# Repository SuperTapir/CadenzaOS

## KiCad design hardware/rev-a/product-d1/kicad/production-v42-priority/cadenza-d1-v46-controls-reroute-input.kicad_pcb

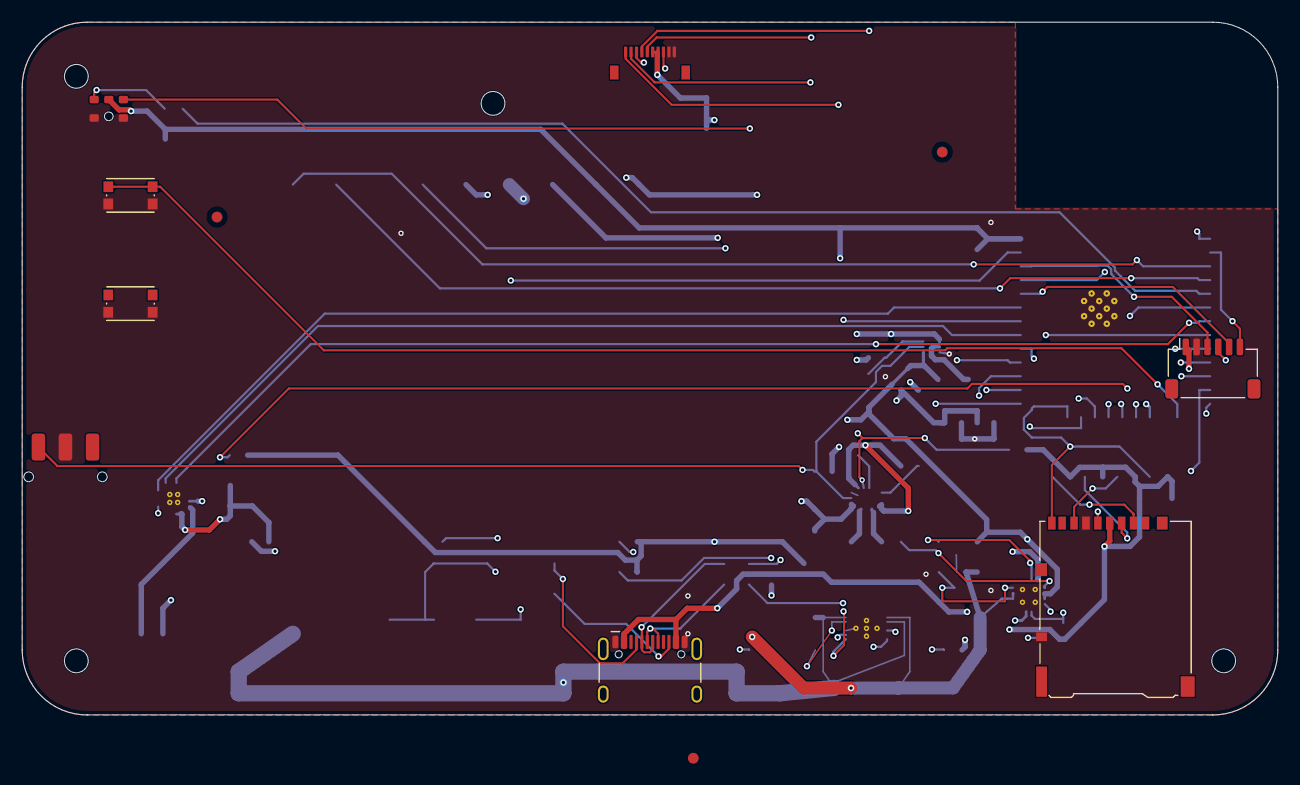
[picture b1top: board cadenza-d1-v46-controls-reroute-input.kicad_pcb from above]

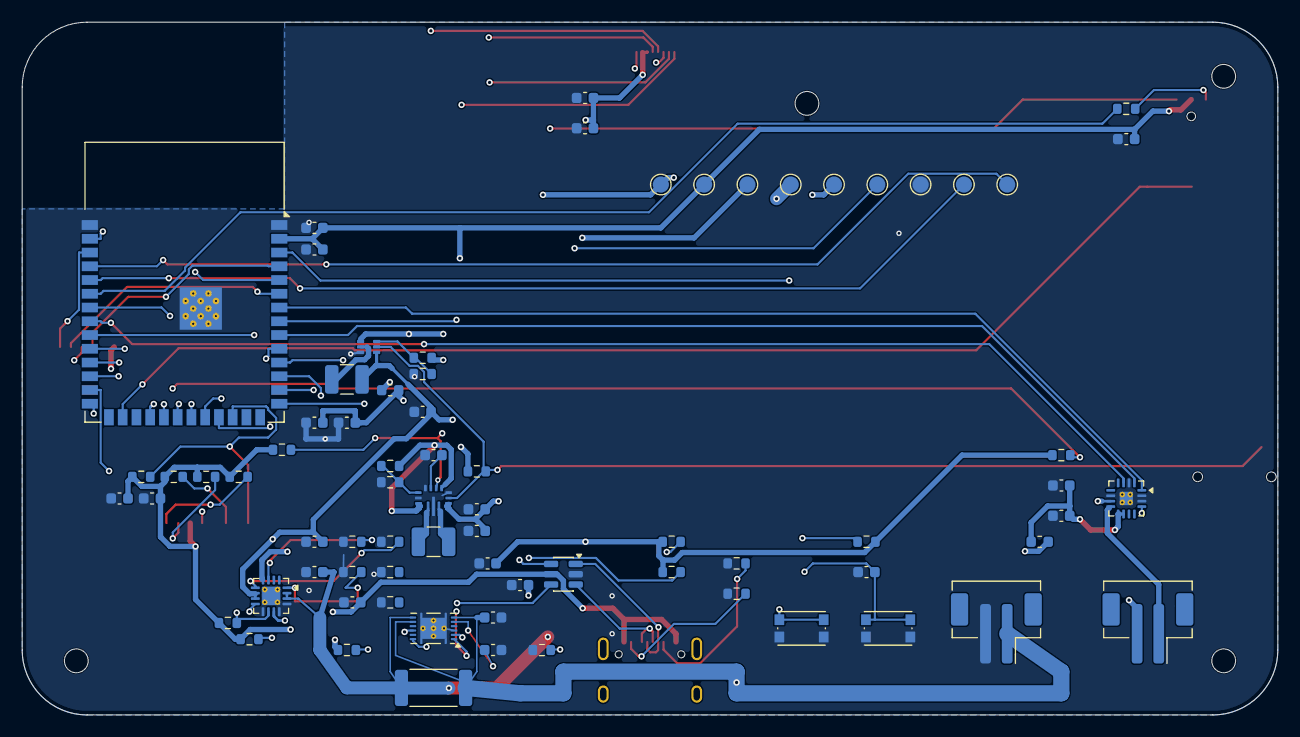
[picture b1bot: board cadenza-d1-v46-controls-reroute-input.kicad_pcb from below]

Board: 4 copper layers, 116.0 x 64.0 mm, 90 parts (74 on the bottom side), 65 nets.

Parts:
C1, C2, C3, C10, C11, C20, C50, C81, C90: 10uF
C12, C13, C21, C22: 22uF
C14, C31, C40, C51, C82, C91: 100nF
C30, C70, C71, C80: 1uF
FB1, FB2: 600R@100MHz
FID1, FID2, FID3: Fiducial; Fiducial_1mm_Mask2mm
H1, H2, H3, H4: NPTH 2.2mm
J1: USB-C USB2 Sink
J2: LS027B7DH01 FPC
J3: microSD push-push
J4: LiPo 1S
J5: Speaker 8R 1-2W
J6: Encoder daughterboard
L1: 1.2uH Isat>=4.5A
L2: 1uH Isat>=4.5A
LCD1: LS027B7DH01 62.8x42.82
R1, R2: 5.1k
R3, R5: 1.5k
R4: 1.18k
R6: 47k
R7, R72, R74, R80, R90, R91, R92, R93: 10k
R10: 470k
R11: 150k
R20: 732k
R21, R30, R41, R75, R76, R77: 100k
R40: 100R
R70, R71: 4.7k
R73: 0.01R 1% 1W 50ppm; R_2512_6332Metric
SW1: POWER RUN/OFF
SW2: B
SW3: MENU
SW4: RESET
SW5: BOOT
TP1: UART_TX0; TestPoint_Pad_D1.5mm
TP2: UART_RX0; TestPoint_Pad_D1.5mm
TP3: GND; TestPoint_Pad_D1.5mm
TP4: PG_3V3; TestPoint_Pad_D1.5mm
TP5: PACKP; TestPoint_Pad_D1.5mm
TP6: VBAT; TestPoint_Pad_D1.5mm
TP7: VSYS; TestPoint_Pad_D1.5mm
TP8: +3V3; TestPoint_Pad_D1.5mm
TP9: +5V; TestPoint_Pad_D1.5mm
U1: ESP32-S3-WROOM-1-N16R8
U2: BQ24074RGTR
U3: TPS63070RNMR
U4: TPS61023DRLR
U5: MAX98357AETE+T
U6: IM73D122V01
U7: BQ27441DRZR-G1A
U8: USBLC6-2SC6

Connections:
/+3V3_MAIN: C12.1, C13.1, C40.1, C81.1, C82.1, C90.1, C91.1, J3.4 (VDD), J6.1, R10.1, R41.2, R70.2, R71.2, R74.2, R75.2, R76.2, R77.2, R80.1, R90.2, R91.2, R92.2, R93.2, TP8.1, U1.2 (3V3), U3.1 (PS_SYNC), U3.7 (VOUT), U3.8 (VOUT), U6.2 (VDD)
/+5V_AUDIO: C50.1, C51.1, FB2.2, U5.7 (VDD), U5.8 (VDD)
/+5V_LCD: C30.1, C31.1, FB1.2, J2.6 (VDDA), J2.7 (VDD)
/+5V_MEDIA: C21.1, C22.1, FB1.1, FB2.1, R20.1, TP9.1, U4.6 (VOUT)
/AMP_EN: R41.1, U1.34 (GPIO41), U5.4 (SD_MODE)
/A_SW: J6.5, U1.6 (GPIO6)
/BAT_TS: R7.1, U2.1 (TS)
/BOOST_SW: L2.2, U4.5 (SW)
/BOOT_N: SW5.1 (A), U1.27 (GPIO0)
/B_SW: SW2.1 (A), U1.24 (GPIO47)
/CC1: J1.A5 (CC1), R1.1
/CC2: J1.B5 (CC2), R2.1
/CHG_N: R77.1, U1.10 (GPIO17), U2.9 (CHG)
/ENC_A: J6.3, U1.4 (GPIO4)
/ENC_B: J6.4, U1.5 (GPIO5)
/ESP_EN: C80.1, R80.2, SW4.1 (A), U1.3 (EN)
/FB_3V3: R10.2, R11.1, U3.5 (FB)
/FB_5V: R20.2, R21.1, U4.1 (FB)
/GAUGE_BIN: R72.1, U7.10 (NC)
/GAUGE_INT_N: R74.1, U1.23 (GPIO21), U7.12 (GPOUT)
/GAUGE_VDD: C71.1, U7.5 (SCL)
/GND: C1.2, C2.2, C3.2, C10.2, C11.2, C12.2, C13.2, C14.2, C20.2, C21.2, C22.2, C30.2, C31.2, C40.2, C50.2, C51.2, C70.2, C71.2, C80.2, C81.2, C82.2, C90.2, C91.2, J1.A1 (GND), J1.A12 (GND), J1.B1 (GND), J1.B12 (GND), J2.9 (VSS), J2.10 (VSSA), J3.6 (VSS), J3.10 (SHIELD), J4.2, J6.2, R1.2, R2.2, R3.2, R4.2, R5.2, R6.2, R7.2, R11.2, R21.2, R72.2, SW1.2 (B), SW2.2 (B), SW3.2 (B), SW4.2 (B), SW5.2 (B), TP3.1, U1.1 (GND), U1.40 (GND), U1.41 (EPAD), U2.4 (CE), U2.5 (EN2), U2.8 (VSS), U2.17 (EP), U3.4 (GND), U3.6 (FB2), U3.10 (PGND), U3.15 (VSEL), U4.4 (GND), U5.2 (GAIN_SLOT), U5.3 (GND), U5.11 (GND), U5.15 (GND), U5.17 (EP), U6.4 (LR), U6.5 (GND), U7.3 (NC), U7.13 (EP), U8.2 (GND)
/I2C_SCL: R71.1, U1.11 (GPIO18), U7.2 (VDD)
/I2C_SDA: R70.1, U1.12 (GPIO8), U7.1 (SDA)
/I2S_BCLK: U1.9 (GPIO16), U5.16 (BCLK)
/I2S_DIN: U1.7 (GPIO7), U5.1 (DIN)
/I2S_LRCLK: U1.33 (GPIO40), U5.14 (LRCLK)
/ILIM_SET: R3.1, U2.12 (ILIM)
/ISET_SET: R4.1, U2.16 (ISET)
/ITERM_SET: R5.1, U2.15 (ITERM)
/L3V3_A: L1.1, U3.11 (L1)
/L3V3_B: L1.2, U3.9 (L2)
/LCD_DISP: J2.5 (DISP), U1.21 (GPIO13)
/LCD_EXTCOMIN: J2.4 (EXTCOMIN), U1.22 (GPIO14)
/LCD_EXTMODE: J2.8 (EXTMODE), U1.8 (GPIO15)
/LCD_SCLK: J2.1 (SCLK), U1.20 (GPIO12)
/LCD_SCS: J2.3 (SCS), U1.18 (GPIO10)
/LCD_SI: J2.2 (SI), U1.19 (GPIO11)
/LED_CTRL: J6.6, U1.38 (GPIO2)
/MENU_SW: SW3.1 (A), U1.25 (GPIO48)
/PACKP: C70.1, J4.1, R73.2, TP5.1, U7.6 (BAT), U7.8 (NC)
/PDM_CLK: U1.32 (GPIO39), U6.3 (CLOCK)
/PDM_DATA: R40.2, U1.35 (GPIO42)
/PDM_DATA_RAW: R40.1, U6.1 (DATA)
/PGOOD_N: R75.1, U1.39 (GPIO1), U2.7 (PGOOD)
/PG_3V3_N: R76.1, TP4.1, U3.2 (PG)
/RUN_EN: R30.1, SW1.1 (A), U3.14 (EN), U4.2 (EN)
/SD_CD: J3.9 (CD), R93.1, U1.17 (GPIO9)
/SD_CLK: J3.5 (CLK), U1.29 (GPIO36)
/SD_CMD: J3.3 (CMD), R91.1, U1.28 (GPIO35)
/SD_CS: J3.2 (CD_DAT3), R90.1, U1.31 (GPIO38)
/SD_DAT0: J3.7 (DAT0), R92.1, U1.30 (GPIO37)
/SPK+: J5.1, U5.9 (OUTP)
/SPK-: J5.2, U5.10 (OUTN)
/TMR_SET: R6.1, U2.14 (TMR)
/UART_RX0: TP2.1, U1.36 (RXD0)
/UART_TX0: TP1.1, U1.37 (TXD0)
/USB_D+: U1.14 (GPIO20), U8.4 (IO2)
/USB_D+_CONN: J1.A6 (D+), J1.B6 (D+), U8.3 (IO2)
/USB_D-: U1.13 (GPIO19), U8.6 (IO1)
/USB_D-_CONN: J1.A7 (D-), J1.B7 (D-), U8.1 (IO1)
/VAUX_3V3: C14.1, U3.3 (VAUX)
/VBAT: C3.1, R73.1, TP6.1, U2.2 (BAT), U2.3 (BAT), U7.7 (SRN)
/VBUS: C1.1, J1.A4 (VBUS), J1.A9 (VBUS), J1.B4 (VBUS), J1.B9 (VBUS), U2.13 (IN), U8.5 (VBUS)
/VSYS: C2.1, C10.1, C11.1, C20.1, L2.1, R30.2, TP7.1, U2.6 (EN1), U2.10 (OUT), U2.11 (OUT), U3.12 (VIN), U3.13 (VIN), U4.3 (VIN)
